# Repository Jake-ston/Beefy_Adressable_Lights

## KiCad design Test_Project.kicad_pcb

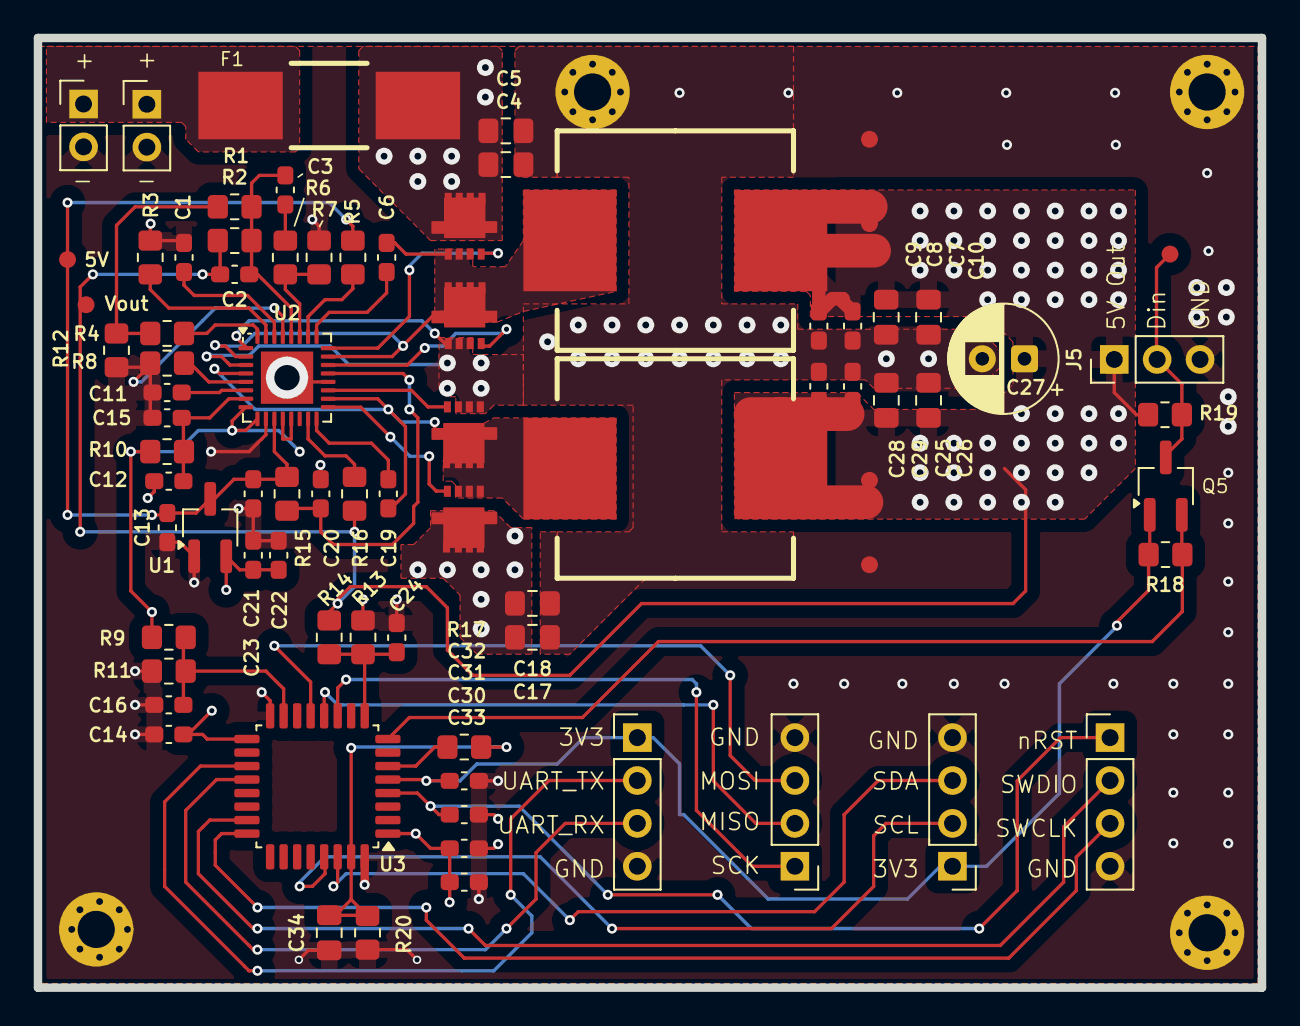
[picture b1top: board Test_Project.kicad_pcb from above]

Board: 4 copper layers, 72.5 x 56.2 mm, 72 parts (0 on the bottom side), 44 nets.

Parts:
C1, C3, C6, C9, C12, C14, C19, C23, C28, C30, C31, C32: 100nF; C_0603_1608Metric_Pad1.08x0.95mm_HandSolder
C2, C8, C13, C16, C22, C24, C29, C33: 1uF; C_0603_1608Metric_Pad1.08x0.95mm_HandSolder
C4, C5, C7, C10, C17, C18, C25, C26, C34: 22uF; C_0805_2012Metric_Pad1.18x1.45mm_HandSolder
C11: 100pF; C_0603_1608Metric_Pad1.08x0.95mm_HandSolder
C15: ?uF; C_0603_1608Metric_Pad1.08x0.95mm_HandSolder
C20, C21: 4.7uF; C_0603_1608Metric_Pad1.08x0.95mm_HandSolder
C27: 100uF; CP_Radial_D6.3mm_P2.50mm
F1: 0678L9300-02; Fuse - 0678L9300-02
J1, J2: Conn_01x02; PinHeader_1x02_P2.54mm_Vertical
J3, J4, J6, J7: Conn_01x04; PinHeader_1x04_P2.54mm_Vertical
J5: Conn_01x03; PinHeader_1x03_P2.54mm_Vertical
L1, L2: 2.2uH; SRP1265A
Q1, Q2, Q3, Q4: NTTFS5C454NLTAG
Q5: BSS138-7-F
R1, R12, R17: 3.3kΩ; R_0805_2012Metric_Pad1.20x1.40mm_HandSolder
R2, R5, R11, R13, R16: 10kΩ; R_0805_2012Metric_Pad1.20x1.40mm_HandSolder
R3, R8, R14, R18, R19: 25.5 kΩ; R_0805_2012Metric_Pad1.20x1.40mm_HandSolder
R4, R6, R7, R9, R10: 100kΩ; R_0805_2012Metric_Pad1.20x1.40mm_HandSolder
R15: 2.2Ω; R_0805_2012Metric_Pad1.20x1.40mm_HandSolder
R20: 1M; R_0805_2012Metric_Pad1.20x1.40mm_HandSolder
U1: AP2127N-3.3TRG1; SOT-23W_Handsoldering
U2: MIC2132YML; QFN-32-1EP_5x5mm_P0.5mm_EP3.1x3.1mm
U3: STM32L081KZT6; LQFP-32_7x7mm_P0.8mm

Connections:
/12V: F1.1, J1.1, J2.1
/Boot0: C34.1, R17.2, R20.1, U3.31 (BOOT0)
/Bootloader_On_Reset: R17.1, U3.6 (PA0)
/I2C_SCL: J7.2, U3.29 (PB6)
/I2C_SDA: J7.3, U3.30 (PB7)
/LED_Data_Out (PWM): Q5.2 (S), R18.1, U3.8 (PA2)
/SPI_MISO: J6.2, U3.12 (PA6)
/SPI_MOSI: J6.3, U3.13 (PA7)
/SPI_SCK: J6.1, U3.11 (PA5)
/SWCLK: J4.3, U3.24 (PA14)
/SWDIO: J4.2, U3.23 (PA13)
/USART_RX: J3.3, U3.20 (PA10)
/USART_TX: J3.2, U3.19 (PA9)
/VDD_3V3: C14.1, C22.1, C23.1, C30.1, C32.1, C33.1, J3.1, J7.1, Q5.3 (G), R18.2, U1.2 (VO), U3.1 (VDD), U3.5 (VDDA), U3.17 (VDD)
/VDD_5V: C13.1, C21.1, R5.2, R15.2, U1.3 (VI), U2.11 (EXTVDD)
/Vin: C4.1, C5.1, C17.1, C18.1, F1.2, Q1.1 (D), Q4.1 (D), R9.2, R10.2, U2.8 (VIN), U2.9 (VDD)
/Vin_ADC: C16.1, R9.1, R11.2, U3.15 (PB1)
/Vout: C2.1, C7.1, C8.1, C9.1, C10.1, C25.1, C26.1, C27.1, C28.1, C29.1, J5.1, L1.2, L2.2, R2.2, R14.2, R16.1, R19.2
/Vout_ADC: C24.1, R13.2, R14.1, U3.9 (PA3)
/nRST: C31.1, J4.1, U3.4 (NRST)
GND: C1.1, C4.2, C5.2, C7.2, C8.2, C9.2, C10.2, C11.1, C12.2, C13.2, C14.2, C15.2, C16.2, C17.2, C18.2, C20.2, C21.2, C22.2, C23.2, C24.2, C25.2, C26.2, C27.2, C28.2, C29.2, C30.2, C31.2, C32.2, C33.2, C34.2, J1.2, J2.2, J3.4, J4.4, J5.3, J6.4, J7.4, Q2.2 (S), Q3.2 (S), R3.1, R7.2, R8.1, R11.1, R12.1, R13.1, R20.2, U1.1 (GND), U2.1 (CSN2), U2.3 (CSN1), U2.10 (AGND), U2.20 (PGND), U2.29 (GFB), U2.33 (PAD), U3.16 (VSS), U3.32 (VSS)
unnamed: C3.2, R6.2
unnamed: J5.2, Q5.1 (D), R19.1
unnamed: Q4.3 (G), U2.17 (DH1)
unnamed: C19.1, L2.1, Q3.1 (D), Q4.2 (S), U2.4 (CSP1), U2.18 (SW1)
unnamed: Q3.3 (G), U2.19 (DL1)
unnamed: Q1.3 (G), U2.24 (DH2)
unnamed: C6.1, L1.1, Q1.2 (S), Q2.1 (D), U2.2 (CSP2), U2.23 (SW2)
unnamed: Q2.3 (G), U2.22 (DL2)
unnamed: R1.1, R4.2, R12.2
unnamed: U2.12 (NPI), U2.13 (APO)
unnamed: C19.2, U2.16 (BST1)
unnamed: C6.2, U2.25 (BST2)
unnamed: C11.2, U2.6 (CSH)
unnamed: R4.1, U2.32 (DROPP)
unnamed: C12.1, C15.1, R10.1, U2.7 (EN)
unnamed: C2.2, C3.1, R1.2, R2.1, U2.28 (FBS)
unnamed: R3.2, U2.31 (FREQ)
unnamed: R8.2, U2.5 (ILIM)
unnamed: R16.2, U2.15 (OUTS)
unnamed: R5.1, U2.26 (PG)
unnamed: C20.1, R15.1, U2.21 (PVDD)
unnamed: R6.1, R7.1, U2.27 (RIP_INJ)
unnamed: C1.2, U2.30 (SS)

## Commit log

2025-05-27 First commit. Nothing functional, just testing things out.
2025-05-27 Learned how to export footprints to local library so things are portable. PCB editor -> export -> footprints to library Modified .gitignore to keep track of this library
2025-05-28 Daily commit
2025-05-29 Added a local symbol library to match how the PCB footprints are stored. Again, with portability in mind.
    This update of footprints and schematic symbols should be done whenever something else is added.
2025-05-30 Worked on switching converter portion of schematic. Still needs deciding: RDROOP Cout RIlim Cin Bootstrap caps MOSFETs
    MOSFET based level shifter for the LED strip.
2025-05-30 Finished up buck section of schematic minus the mosfet choice. Also moved around things on the schematic and added an optional electrolytic capacitor
2025-05-30 Added values to the input decoupling capacitors on the top set of fets
2025-05-30 Finished up schematic
2025-05-30 Added part number for transistors. Need to create footprint and reconsider R_{ILIM}
2025-06-02 Added preliminary footprint for the MOSFETs
2025-06-02 Started PCB layout
2025-06-03 Removed the 12V jack, added another 0.1" header in parallel so more current can be achieved if there are issues. Did most of the PCB layout. Updated some footprints
2025-06-03 Finished up routing nets and pouring polygons. Needs final ground pours and review before ordering.
2025-06-05 Added BOM and digikey cart order.
2025-06-05 Finished up layout and added some mounting holes.
2025-06-05 Daily commit. Working through test points and DRC checks.
2025-06-09 Modified footprints, redid silkscreen designators to be geographical on PCB rather than on schematic (experimental) Started process of DRC. Will need to check against JLC's requirements (should be go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
2025-06-13 Updated footprint 3d models in local library.
2025-06-17 Generated gerbers and drill files
2025-07-08 Generated PDFs
